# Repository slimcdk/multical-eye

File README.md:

# IR Eye for Kamstrup MultiCal

## Production files

## Contribution

Clone repository and fetch submodules

```bash
$ git clone --recursive-submodules git@github.com:slimcdk/multical-eye.git
```

## Versioning

Revisions are controlled through git tags such any production easily can be traced back to a commit containing everything. Complete sets of compatible schematics, PCB layouts, documentations, 3D models etc will all stay together under same tag in the source history.

---

## Software uses

* https://www.kicad.org/
* https://www.freecadweb.org/
* https://github.com/features/actions
  * https://github.com/INTI-CMNB/KiBot
* https://code.visualstudio.com/
  * https://marketplace.visualstudio.com/items?itemName=ms-vscode-remote.remote-containers

## Notes

### Parts

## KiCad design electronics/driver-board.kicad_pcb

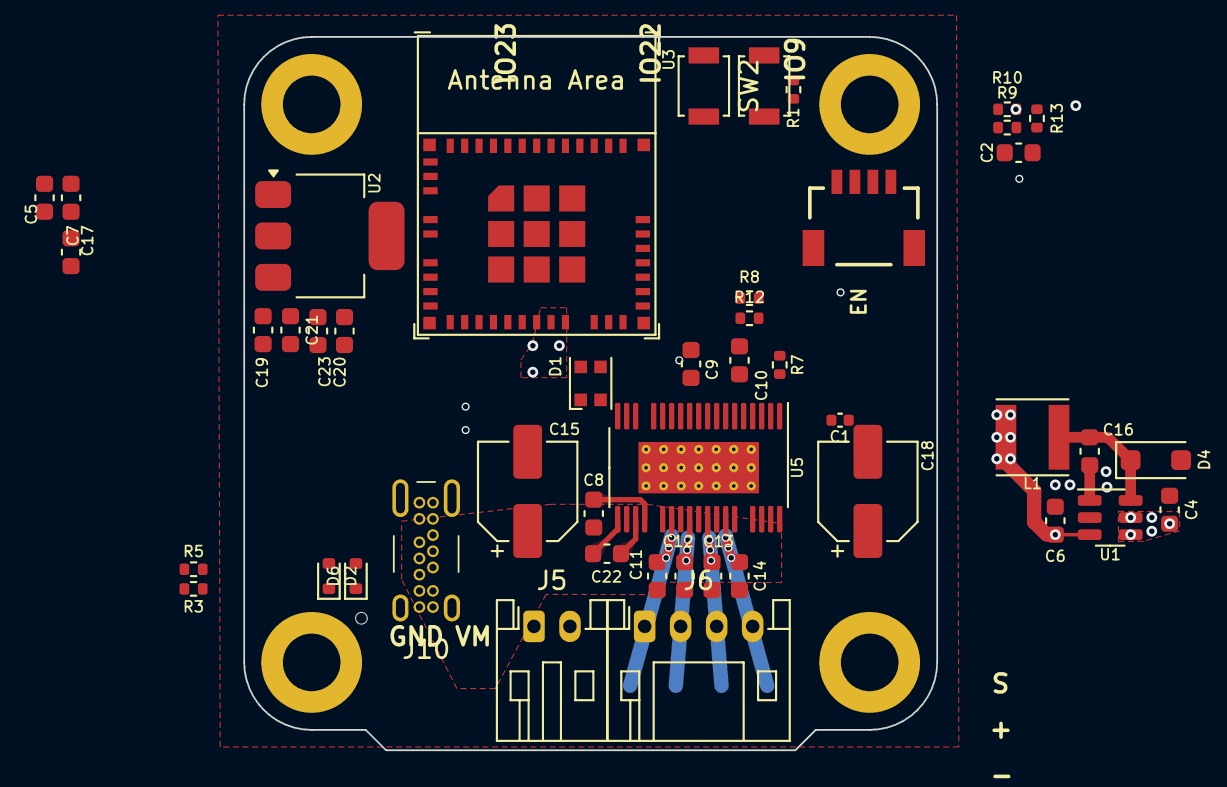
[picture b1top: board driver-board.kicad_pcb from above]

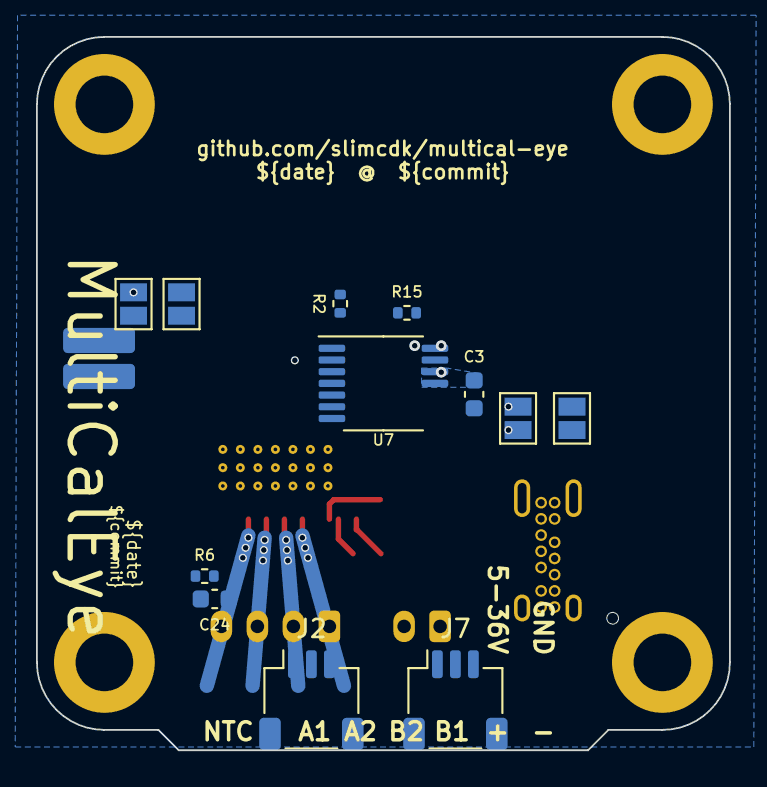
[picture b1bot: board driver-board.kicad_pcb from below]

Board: 4 copper layers, 38.5 x 39.6 mm, 63 parts (13 on the bottom side), 42 nets.

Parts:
C1: 100nF; C_0402_1005Metric
C2, C7, C8, C13, C14: 1µF; C_0603_1608Metric
C3, C9, C11, C12, C16, C17, C19, C23, C24: 100nF; C_0603_1608Metric
C4, C10: 2.2µF; C_0603_1608Metric
C5, C6, C20, C21: 10µF; C_0603_1608Metric
C15, C18: 33µF; CP_Elec_5x5.9
C22: 22nF; C_0603_1608Metric
D1: WS2812B; LED_WS2812B-2020_PLCC4_2.0x2.0mm
D2, D6: LESD5D5; D_SOD-523
D4: DS210W; D_SOD-123F
H1, H2, H3, H4: M3 MountingHole; MountingHole_3.2mm_M3_DIN965_Pad
J1: Conn_01x02; PinHeader_1x02_P2.00mm_Vertical_SMD_Pin1Left
J2, J7: Conn_01x03; JST_SH_SM03B-SRSS-TB_1x03-1MP_P1.00mm_Horizontal
J4: Qwiic_RA; JST_SMD_1.0mm-4_RA
J5: Conn_01x02; JST_PH_S2B-PH-K_1x02_P2.00mm_Horizontal
J6: Conn_01x04; JST_PH_S4B-PH-K_1x04_P2.00mm_Horizontal
J10: USB_C_Receptacle_USB2.0; USB_C_GT-USB-7036A
JP1, JP2, JP3, JP4: Jumper_2_Open; SolderJumper-2_P1.3mm_Open_Pad1.0x1.5mm
L1: 6.8µH; L_Vishay_IFSC-1515AH_4x4x1.8mm
R1, R2, R6, R8, R9, R10, R12, R13, R15: 10k; R_0402_1005Metric
R3, R5: 5k1; R_0402_1005Metric
R7: 12k; R_0402_1005Metric
SW1, SW2: SW_Push; SW_SPST_B3U-1000P
U1: LMR16006YQ3; SOT-23-6
U2: AMS1117-3.3; SOT-223-3_TabPin2
U3: ESP32-C6-MINI-1/U; ESP32-C6-MINI-1
U5: TMC5240-TSSOP38; TSSOP-38_4.4x9.7mm_P0.5mm
U7: AS5047D; TSSOP-14_4.4x5mm_P0.65mm

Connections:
+3V3: C1.1, C3.2, C5.2, C6.2, C7.2, C9.2, C17.2, C20.2, C23.1, D1.1 (VDD), J2.2, J4.2, J7.2, L1.2, R1.2, R2.2, R6.2, R8.2, R9.2, R10.2, R12.2, R13.2, U1.3 (FB), U2.2 (VO), U3.3 (3V3), U5.11 (VCC_IO), U7.11 (VDD), U7.12 (VDD3V3)
+5V: C19.1, C21.2, J10.A4 (VBUS), J10.A9 (VBUS), J10.B4 (VBUS), J10.B9 (VBUS), U2.3 (VI)
/AS_ENCA: JP1.1 (A), U5.14 (ENCA), U7.7 (A)
/AS_ENCB: JP2.1 (A), U5.13 (ENCB), U7.6 (B)
/AS_ENCN: U5.12 (ENCN), U7.14 (I/PWM)
/ESP_BOOT: R1.1, SW2.2, U3.23 (GPIO9)
/ESP_EN: C2.1, R13.1, SW1.1, U3.8 (EN/CHIP_PU)
/ESP_GPIO0: R15.1, U3.12 (GPIO0/ADC1_CH0/XTAL_32K_P), U5.15 (DRV_EN)
/ESP_GPIO1: JP1.2 (B), U3.13 (GPIO1/ADC1_CH1/XTAL_32K_N)
/ESP_GPIO2: D1.4 (DIN), U3.5 (GPIO2/ADC1_CH2)
/ESP_GPIO3: JP2.2 (B), U3.6 (GPIO3/ADC1_CH3)
/ESP_GPIO4: U3.9 (MTMS/GPIO4/ADC1_CH4), U5.18 (DIAG1/SW)
/ESP_GPIO5: U3.10 (MTDI/GPIO5/ADC1_CH5), U5.17 (DIAG0)
/ESP_GPIO6: U3.15 (MTCK/GPIO6/ADC1_CH6), U5.2 (SDO/NAO), U7.3 (MISO)
/ESP_GPIO7: R2.1, U3.16 (MTDO/GPIO7), U7.1 (~CS)
/ESP_GPIO8: U3.22 (GPIO8), U5.38 (SCK/AD1), U7.2 (CLK)
/ESP_GPIO12: D2.2 (A2), J10.A7 (D-), J10.B7 (D-), U3.17 (GPIO12/USB_D-)
/ESP_GPIO13: D6.2 (A2), J10.A6 (D+), J10.B6 (D+), U3.18 (GPIO13/USB_D+)
/ESP_GPIO14: U3.19 (GPIO14), U5.1 (SDI/AD0), U7.4 (MOSI)
/ESP_GPIO15: U3.20 (GPIO15), U5.36 (CS/AD2)
/ESP_GPIO16: J4.4, R10.1, U3.31 (U0TXD/GPIO16)
/ESP_GPIO17: J4.3, R9.1, U3.30 (U0RXD/GPIO17)
/ESP_GPIO20: JP4.2 (B), U3.26 (GPIO20)
/ESP_GPIO21: JP3.1 (A), U3.27 (GPIO21)
/TMC_AIN: C24.2, J1.2, R6.1, U5.8 (AIN)
/TMC_OUT1A: J6.4, U5.32 (OUT1A)
/TMC_OUT1B: J6.2, U5.26 (OUT1B)
/TMC_OUT2A: J6.3, U5.30 (OUT2A)
/TMC_OUT2B: J6.1, U5.28 (OUT2B)
/TMC_REFL: J2.3, JP3.2 (B), R8.1, U5.5 (REFL)
/TMC_REFR: J7.3, JP4.1 (A), R12.1, U5.6 (REFR)
/USB_CC1: J10.A5 (CC1), R5.1
/USB_CC2: J10.B5 (CC2), R3.1
GND: C1.2, C2.2, C3.1, C4.1, C5.1, C6.1, C7.1, C9.1, C10.1, C11.2, C12.2, C13.2, C14.2, C15.2, C17.1, C18.2, C19.2, C20.1, C21.1, C23.2, C24.1, D1.3 (VSS), D2.1 (A1), D4.2 (A), D6.1 (A1), J1.1, J2.1, J4.1, J5.1, J7.1, J10.A1 (GND), J10.A12 (GND), J10.B1 (GND), J10.B12 (GND), R3.2, R5.2, R7.2, R15.2, SW1.2, SW2.1, U1.2 (GND), U2.1 (GND), U3.1 (GND), U3.2 (GND), U3.11 (GND), U3.14 (GND), U3.36 (GND), U3.37 (GND), U3.38 (GND), U3.39 (GND), U3.40 (GND), U3.41 (GND), U3.42 (GND), U3.43 (GND), U3.44 (GND), U3.45 (GND), U3.46 (GND), U3.47 (GND), U3.48 (GND), U3.49 (GND), U3.50 (GND), U3.51 (GND), U3.52 (GND), U3.53 (GND), U5.3 (CLK), U5.10 (AGND), U5.27 (PGND1), U5.31 (PGND2), U5.39 (EP), U7.5 (TST), U7.13 (GND)
unnamed: C16.1, D4.1 (K), L1.1, U1.6 (SW)
unnamed: C16.2, U1.1 (CB)
unnamed: C22.2, U5.20 (CPI)
unnamed: C22.1, U5.22 (CPO)
unnamed: R7.1, U5.7 (IREF)
unnamed: C8.2, U5.23 (VCP)
unnamed: C10.2, U5.9 (VDD1V8)
VM: C4.2, C8.1, C11.1, C12.1, C13.1, C14.1, C15.1, C18.1, J5.2, U1.4 (~SHDN), U1.5 (VIN), U5.25 (VS1), U5.29 (VS2), U5.33 (VS3), U5.35 (SLEEP)

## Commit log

2024-12-30 init project
2024-12-30 added slimc kicad libraries
2025-01-13 Bump actions/checkout from 3 to 4
    Bumps [actions/checkout](https://github.com/actions/checkout) from 3 to 4.
    - [Release notes](https://github.com/actions/checkout/releases)
    - [Changelog](https://github.com/actions/checkout/blob/main/CHANGELOG.md)
    - [Commits](https://github.com/actions/checkout/compare/v3...v4)
    ---
    updated-dependencies:
2025-02-01 Bump dependencies/kicad-libraries from `55f8136` to `181bb6f`
    Bumps [dependencies/kicad-libraries](https://github.com/slimcdk/kicad-libraries) from `55f8136` to `181bb6f`.
    - [Commits](https://github.com/slimcdk/kicad-libraries/compare/55f81361bc8dd6b7d88a2ce77d89c62e44fedfb8...181bb6fb97240dfd16b9811a01fb4454661adac2)
    ---
    updated-dependencies:
    - dependency-name: dependencies/kicad-libraries
    dependency-type: direct:production
2025-03-01 Bump dependencies/kicad-libraries from `55f8136` to `728d879`
    Bumps [dependencies/kicad-libraries](https://github.com/slimcdk/kicad-libraries) from `55f8136` to `728d879`.
    - [Commits](https://github.com/slimcdk/kicad-libraries/compare/55f81361bc8dd6b7d88a2ce77d89c62e44fedfb8...728d8793c17c51385cbfe4111d3b7130f23c0f83)
    ---
    updated-dependencies:
    - dependency-name: dependencies/kicad-libraries
    dependency-type: direct:production
